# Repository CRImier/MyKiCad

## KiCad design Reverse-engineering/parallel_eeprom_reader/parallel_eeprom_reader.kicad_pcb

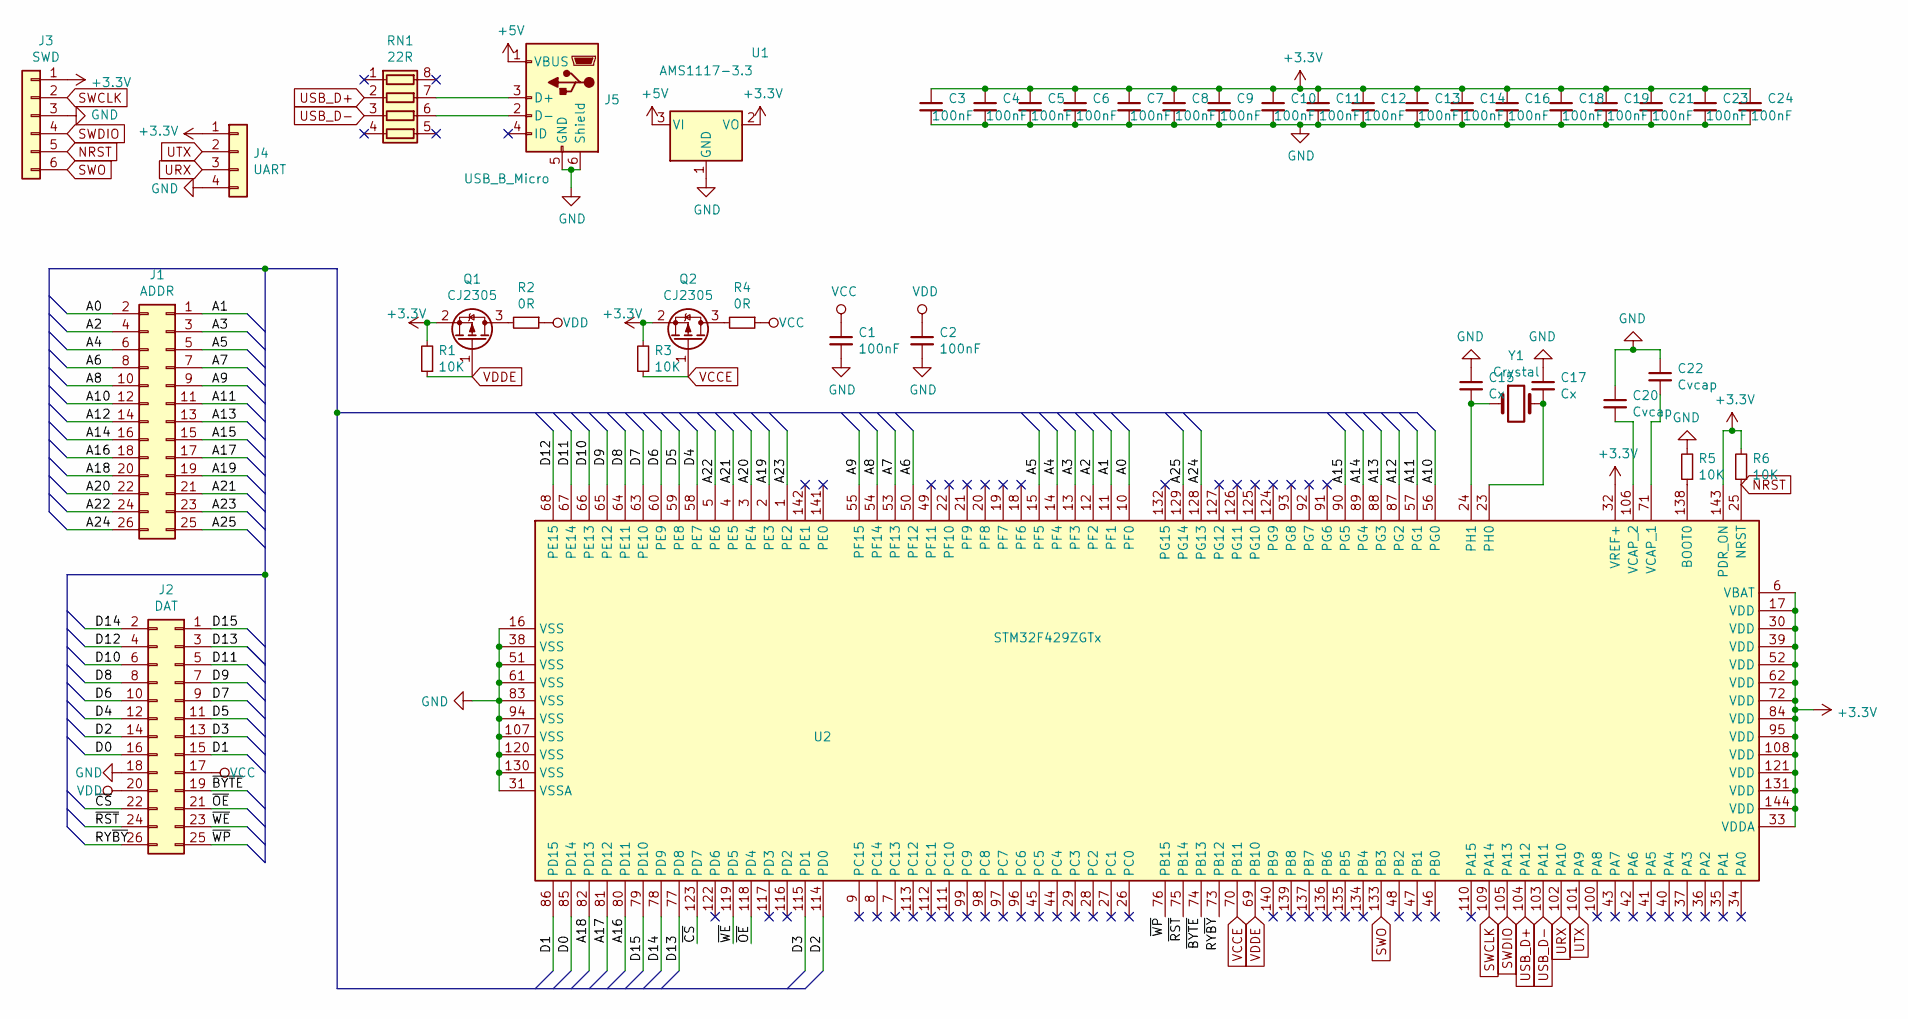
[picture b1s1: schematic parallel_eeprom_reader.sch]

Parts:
C1, C2, C3, C4, C5, C6, C7, C8, C9, C10, C11, C12, C13, C14, C16, C18, C19, C21, C23, C24: 100nF; C_0402_1005Metric
C15, C17: Cx; C_0603_1608Metric
C20, C22: Cvcap; C_0603_1608Metric
J1: ADDR; PinSocket_2x13_P2.00mm_Vertical_SMD
J2: DAT; PinSocket_2x13_P2.00mm_Vertical_SMD
J3: SWD; PinSocket_1x06_P2.54mm_Vertical
J4: UART; PinSocket_2x02_P2.00mm_Vertical
J5: USB_B_Micro; MICROUSB_SIMPLE
Q1, Q2: CJ2305; SOT-23
R1, R3, R5, R6: 10K; R_0402_1005Metric
R2, R4: 0R; R_0402_1005Metric
RN1: 22R; R_Array_Concave_4x0603
U1: AMS1117-3.3; SOT-223-3_TabPin2
U2: STM32F429ZGTx; LQFP-144_20x20mm_P0.5mm
Y1: Crystal; Crystal_SMD_5032-2Pin_5.0x3.2mm_HandSoldering

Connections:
+3V3: C3.1, C4.1, C5.1, C6.1, C7.1, C8.1, C9.1, C10.1, C11.1, C12.1, C13.1, C14.1, C16.1, C18.1, C19.1, C21.1, C23.1, C24.1, J3.1, J4.1, Q1.2 (S), Q2.2 (S), R1.2, R3.2, R6.2, U1.2 (VO), U2.6 (VBAT), U2.17 (VDD), U2.30 (VDD), U2.32 (VREF+), U2.33 (VDDA), U2.39 (VDD), U2.52 (VDD), U2.62 (VDD), U2.72 (VDD), U2.84 (VDD), U2.95 (VDD), U2.108 (VDD), U2.121 (VDD), U2.131 (VDD), U2.143 (PDR_ON), U2.144 (VDD)
+5V: J5.1 (VBUS), U1.3 (VI)
/A0: J1.2, U2.10 (PF0)
/A1: J1.1, U2.11 (PF1)
/A2: J1.4, U2.12 (PF2)
/A3: J1.3, U2.13 (PF3)
/A4: J1.6, U2.14 (PF4)
/A5: J1.5, U2.15 (PF5)
/A6: J1.8, U2.50 (PF12)
/A7: J1.7, U2.53 (PF13)
/A8: J1.10, U2.54 (PF14)
/A9: J1.9, U2.55 (PF15)
/A10: J1.12, U2.56 (PG0)
/A11: J1.11, U2.57 (PG1)
/A12: J1.14, U2.87 (PG2)
/A13: J1.13, U2.88 (PG3)
/A14: J1.16, U2.89 (PG4)
/A15: J1.15, U2.90 (PG5)
/A16: J1.18, U2.80 (PD11)
/A17: J1.17, U2.81 (PD12)
/A18: J1.20, U2.82 (PD13)
/A19: J1.19, U2.2 (PE3)
/A20: J1.22, U2.3 (PE4)
/A21: J1.21, U2.4 (PE5)
/A22: J1.24, U2.5 (PE6)
/A23: J1.23, U2.1 (PE2)
/A24: J1.26, U2.128 (PG13)
/A25: J1.25, U2.129 (PG14)
/D0: J2.16, U2.85 (PD14)
/D1: J2.15, U2.86 (PD15)
/D2: J2.14, U2.114 (PD0)
/D3: J2.13, U2.115 (PD1)
/D4: J2.12, U2.58 (PE7)
/D5: J2.11, U2.59 (PE8)
/D6: J2.10, U2.60 (PE9)
/D7: J2.9, U2.63 (PE10)
/D8: J2.8, U2.64 (PE11)
/D9: J2.7, U2.65 (PE12)
/D10: J2.6, U2.66 (PE13)
/D11: J2.5, U2.67 (PE14)
/D12: J2.4, U2.68 (PE15)
/D13: J2.3, U2.77 (PD8)
/D14: J2.2, U2.78 (PD9)
/D15: J2.1, U2.79 (PD10)
/RY~BY: J2.26, U2.73 (PB12)
/~BYTE: J2.19, U2.74 (PB13)
/~CS: J2.22, U2.123 (PD7)
/~OE: J2.21, U2.118 (PD4)
/~RST: J2.24, U2.75 (PB14)
/~WE: J2.23, U2.119 (PD5)
/~WP: J2.25, U2.76 (PB15)
GND: C1.2, C2.2, C3.2, C4.2, C5.2, C6.2, C7.2, C8.2, C9.2, C10.2, C11.2, C12.2, C13.2, C14.2, C15.1, C16.2, C17.1, C18.2, C19.2, C20.1, C21.2, C22.1, C23.2, C24.2, J2.18, J3.3, J4.4, J5.5 (GND), J5.6 (Shield), R5.2, U1.1 (GND), U2.16 (VSS), U2.31 (VSSA), U2.38 (VSS), U2.51 (VSS), U2.61 (VSS), U2.83 (VSS), U2.94 (VSS), U2.107 (VSS), U2.120 (VSS), U2.130 (VSS)
NRST: J3.5, R6.1, U2.25 (NRST)
unnamed: C15.2, U2.24 (PH1), Y1.1
unnamed: C17.2, U2.23 (PH0), Y1.2
unnamed: C20.2, U2.106 (VCAP_2)
unnamed: C22.2, U2.71 (VCAP_1)
unnamed: J5.2 (D-), RN1.6 (R3.2)
unnamed: J5.3 (D+), RN1.7 (R2.2)
unnamed: Q1.3 (D), R2.2
unnamed: Q2.3 (D), R4.2
unnamed: R5.1, U2.138 (BOOT0)
SWCLK: J3.2, U2.109 (PA14)
SWDIO: J3.4, U2.105 (PA13)
SWO: J3.6, U2.133 (PB3)
URX: J4.3, U2.102 (PA10)
USB_D+: RN1.2 (R2.1), U2.104 (PA12)
USB_D-: RN1.3 (R3.1), U2.103 (PA11)
UTX: J4.2, U2.101 (PA9)
VCC: C1.1, J2.17, R4.1
VCCE: Q2.1 (G), R3.1, U2.70 (PB11)
VDD: C2.1, J2.20, R2.1
VDDE: Q1.1 (G), R1.1, U2.69 (PB10)

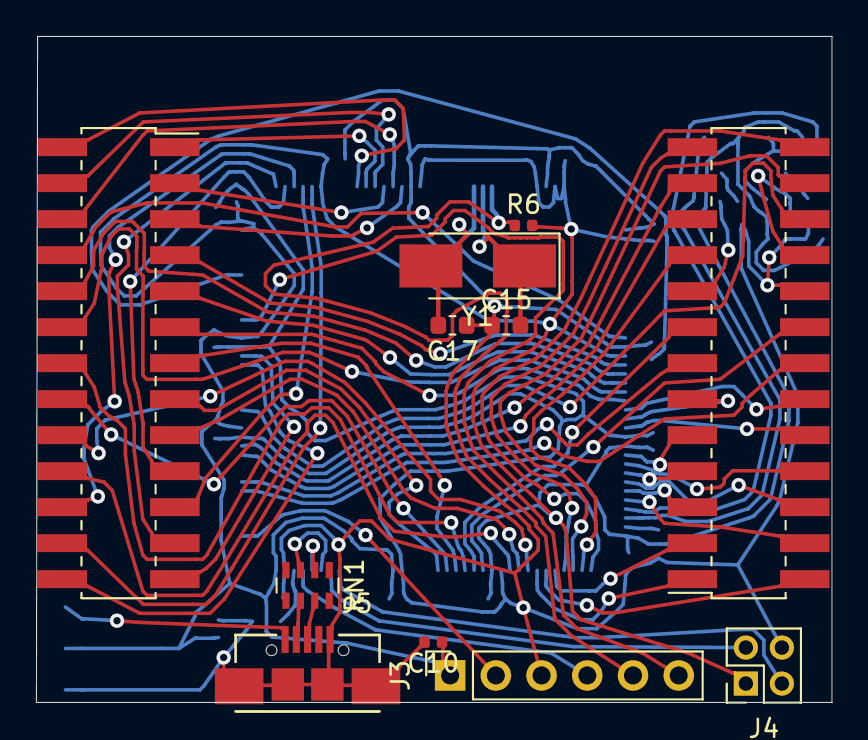
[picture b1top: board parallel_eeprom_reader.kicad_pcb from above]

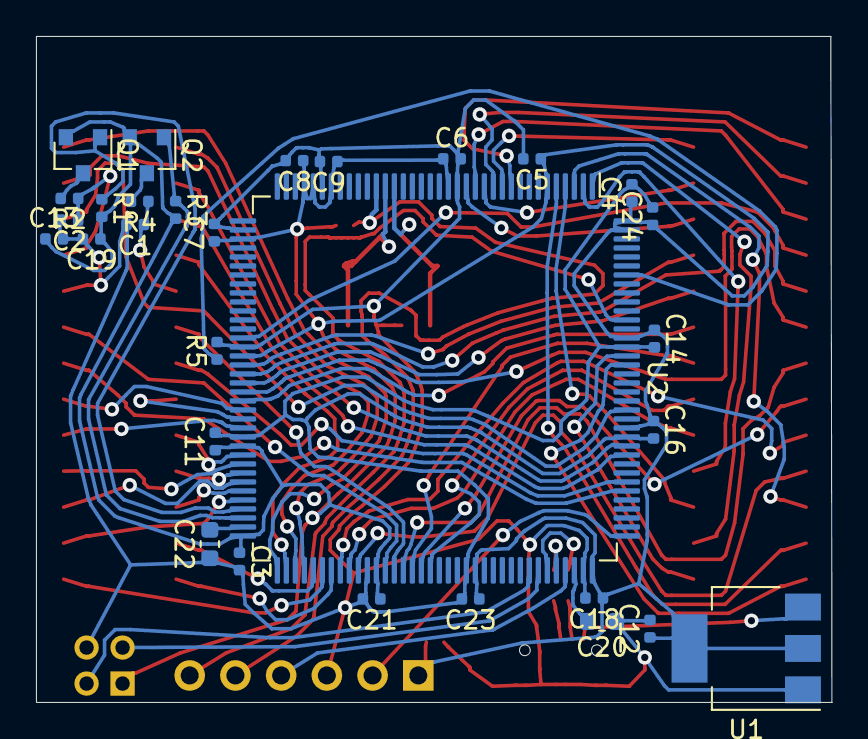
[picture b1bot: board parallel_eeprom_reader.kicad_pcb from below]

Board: 2 copper layers, 44.2 x 37.0 mm, 41 parts (30 on the bottom side), 73 nets.

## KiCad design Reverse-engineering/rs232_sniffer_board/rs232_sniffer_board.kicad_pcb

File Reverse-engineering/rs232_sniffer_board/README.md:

# RS232 sniffer board

An unfinished board for RS232-on-DB9 sniffing, up to 5 RX channels and 3 TX.
Consider it a template. TODO's in the schematic.

Name's Margaret. Likes peaches and popsicles ^~^

## Notes

- This board is untested and there's no guarantees of fitness.

## Info

- Software: Kicad 7
- Version: 0
- PCB size: 76x45mm
- Layer count: 2

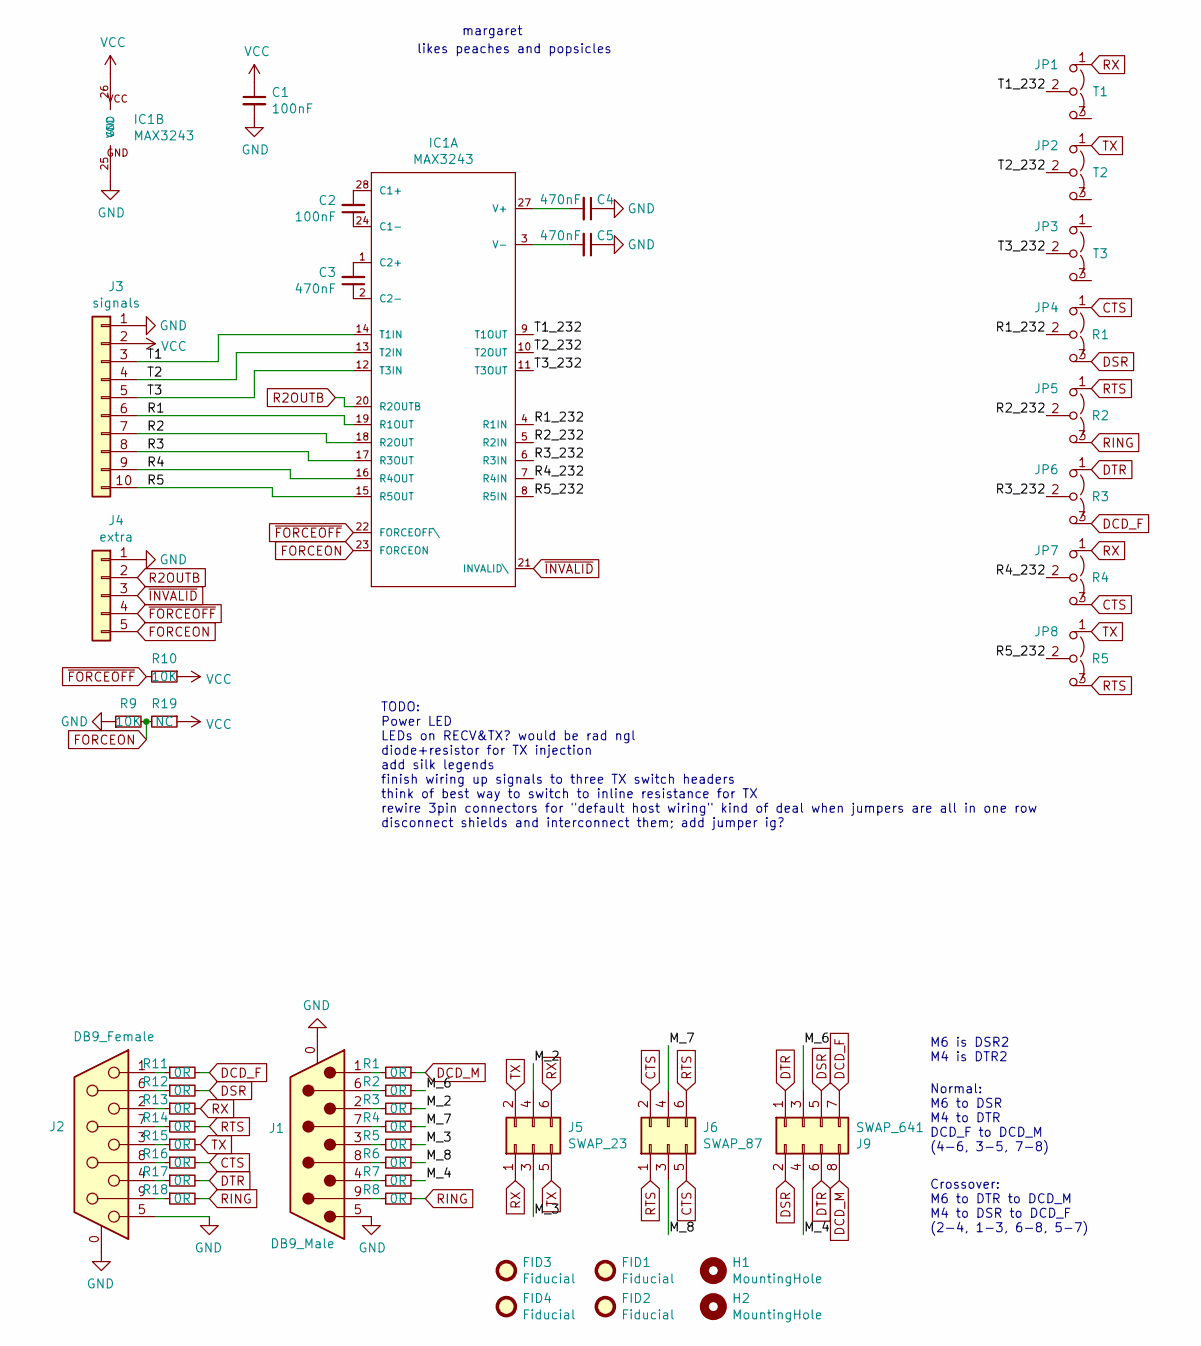
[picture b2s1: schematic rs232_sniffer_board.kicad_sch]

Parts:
C1, C2: 100nF; C_0805_2012Metric
C3, C4, C5: 470nF; C_0805_2012Metric
FID1, FID2, FID3, FID4: Fiducial; Fiducial_1.5mm_Mask3mm
H1, H2: MountingHole; MountingHole_5mm
IC1: MAX3243; SSOP-28_5.3x10.2mm_P0.65mm
J1: DB9_Male; DSUB-9_Male_Horizontal_P2.77x2.84mm_EdgePinOffset4.94mm_Hou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
J2: DB9_Female; DSUB-9_Female_Horizontal_P2.77x2.84mm_EdgePinOffset4.94mm_H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
J3: signals; PinHeader_1x10_P2.54mm_Vertical
J4: extra; PinHeader_1x05_P2.54mm_Vertical
J5: SWAP_23; PinHeader_2x03_P2.54mm_Vertical
J6: SWAP_87; PinHeader_2x03_P2.54mm_Vertical
J9: SWAP_641; PinHeader_2x04_P2.54mm_Vertical
JP1: T1; PinHeader_1x03_P2.54mm_Vertical
JP2: T2; PinHeader_1x03_P2.54mm_Vertical
JP3: T3; PinHeader_1x03_P2.54mm_Vertical
JP4: R1; PinHeader_1x03_P2.54mm_Vertical
JP5: R2; PinHeader_1x03_P2.54mm_Vertical
JP6: R3; PinHeader_1x03_P2.54mm_Vertical
JP7: R4; PinHeader_1x03_P2.54mm_Vertical
JP8: R5; PinHeader_1x03_P2.54mm_Vertical
R1, R2, R3, R4, R5, R6, R7, R8, R11, R12, R13, R14, R15, R16, R17, R18: 0R; R_0805_2012Metric
R9, R10: 10K; R_0805_2012Metric
R19: NC; R_0805_2012Metric

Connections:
/M_2: J5.4, R3.1
/M_3: J5.3, R5.1
/M_4: J9.4, R7.1
/M_6: J9.3, R2.1
/M_7: J6.4, R4.1
/M_8: J6.3, R6.1
/R1: IC1.19 (R1OUT), J3.6
/R1_232: IC1.4 (R1IN), JP4.2 (C)
/R2: IC1.18 (R2OUT), J3.7
/R2_232: IC1.5 (R2IN), JP5.2 (C)
/R3: IC1.17 (R3OUT), J3.8
/R3_232: IC1.6 (R3IN), JP6.2 (C)
/R4: IC1.16 (R4OUT), J3.9
/R4_232: IC1.7 (R4IN), JP7.2 (C)
/R5: IC1.15 (R5OUT), J3.10
/R5_232: IC1.8 (R5IN), JP8.2 (C)
/T1: IC1.14 (T1IN), J3.3
/T1_232: IC1.9 (T1OUT), JP1.2 (C)
/T2: IC1.13 (T2IN), J3.4
/T2_232: IC1.10 (T2OUT), JP2.2 (C)
/T3: IC1.12 (T3IN), J3.5
/T3_232: IC1.11 (T3OUT), JP3.2 (C)
CTS: J6.2, J6.5, JP4.1 (A), JP7.3 (B), R16.2
DCD_F: J9.7, JP6.3 (B), R11.2
DCD_M: J9.8, R1.1
DSR: J9.2, J9.5, JP4.3 (B), R12.2
DTR: J9.1, J9.6, JP6.1 (A), R17.2
FORCEON: IC1.23 (FORCEON), J4.5, R9.2, R19.2
GND: C1.2, C4.1, C5.1, IC1.25 (GND), J1.0 (PAD), J1.5, J2.0 (PAD), J2.5, J3.1, J4.1, R9.1
unnamed: C2.2, IC1.28 (C1+)
unnamed: C2.1, IC1.24 (C1-)
unnamed: C3.2, IC1.1 (C2+)
unnamed: C3.1, IC1.2 (C2-)
unnamed: C4.2, IC1.27 (V+)
unnamed: C5.2, IC1.3 (V-)
unnamed: J1.1, R1.2
unnamed: J1.2, R3.2
unnamed: J1.3, R5.2
unnamed: J1.4, R7.2
unnamed: J1.6, R2.2
unnamed: J1.7, R4.2
unnamed: J1.8, R6.2
unnamed: J1.9, R8.2
unnamed: J2.1, R11.1
unnamed: J2.2, R13.1
unnamed: J2.3, R15.1
unnamed: J2.4, R17.1
unnamed: J2.6, R12.1
unnamed: J2.7, R14.1
unnamed: J2.8, R16.1
unnamed: J2.9, R18.1
R2OUTB: IC1.20 (R2OUTB), J4.2
RING: JP5.3 (B), R8.1, R18.2
RTS: J6.1, J6.6, JP5.1 (A), JP8.3 (B), R14.2
RX: J5.1, J5.6, JP1.1 (A), JP7.1 (A), R13.2
TX: J5.2, J5.5, JP2.1 (A), JP8.1 (A), R15.2
VCC: C1.1, IC1.26 (VCC), J3.2, R10.1, R19.1
~FORCEOFF: IC1.22 (FORCEOFF\), J4.4, R10.2
~INVALID: IC1.21 (INVALID\), J4.3

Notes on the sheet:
margaret
Crossover: M6 to DTR to DCD_M M4 to DSR to DCD_F (2-4, 1-3, 6-8, 5-7)
M6 is DSR2 M4 is DTR2
TODO: Power LED LEDs on RECV&TX? would be rad ngl diode+resistor for TX injection add silk legends finish wiring up signals to three TX switch headers think of best way to switch to inline resistance for TX rewire 3pin connectors for "default host wiring" kind of deal when jumpers are all in one ro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
likes peaches and popsicles
Normal: M6 to DSR M4 to DTR DCD_F to DCD_M (4-6, 3-5, 7-8)

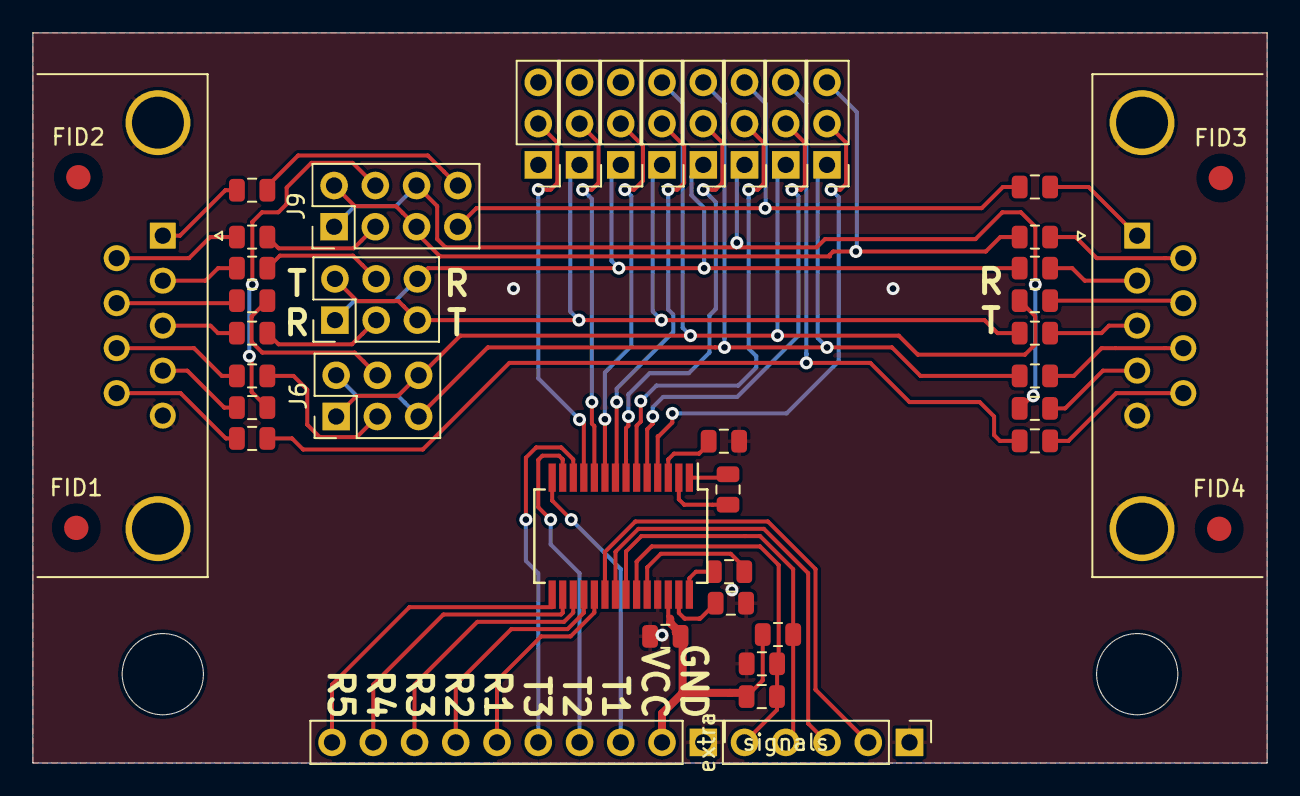
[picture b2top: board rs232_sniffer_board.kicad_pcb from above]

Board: 2 copper layers, 76.0 x 45.0 mm, 46 parts (0 on the bottom side), 59 nets.

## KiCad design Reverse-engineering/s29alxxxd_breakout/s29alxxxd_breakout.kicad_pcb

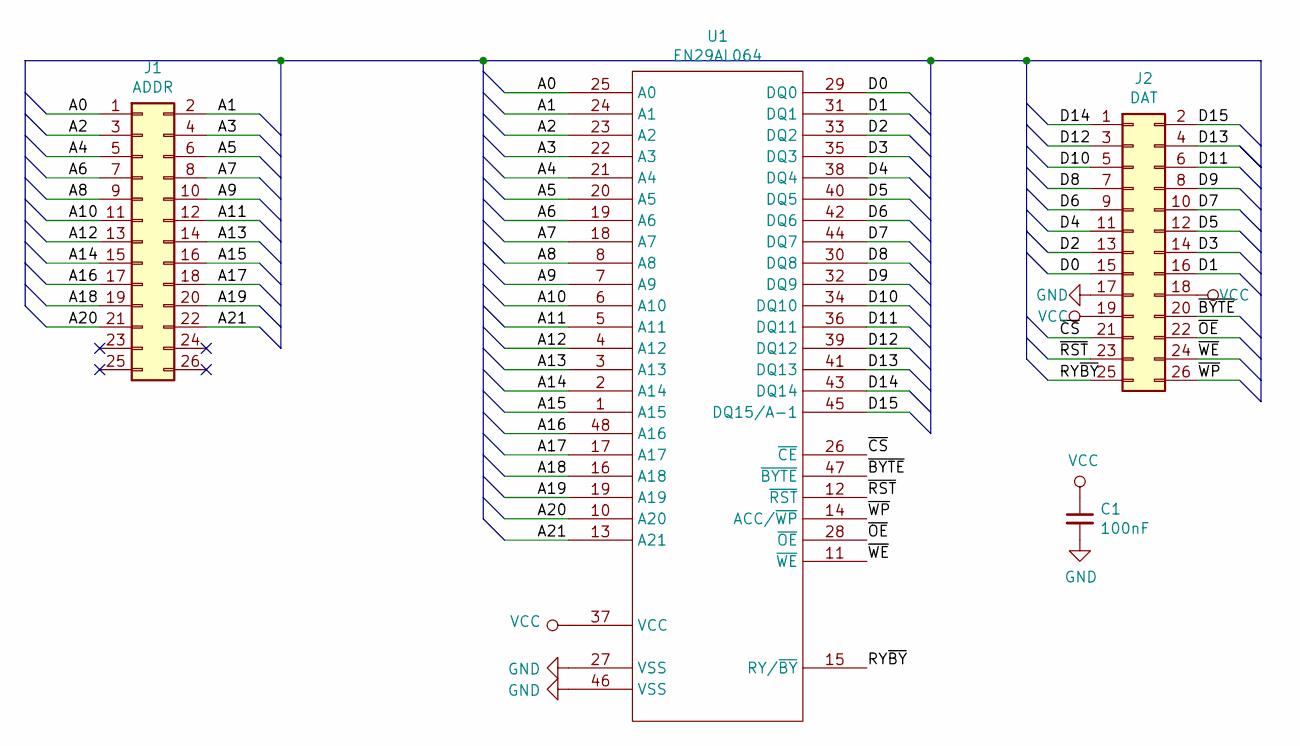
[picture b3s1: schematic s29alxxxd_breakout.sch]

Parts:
C1: 100nF; C_0805_2012Metric
J1: ADDR; PinSocket_2x13_P2.00mm_Vertical_SMD
J2: DAT; PinSocket_2x13_P2.00mm_Vertical_SMD
U1: EN29AL064; TSOP-I-48_18.4x12mm_P0.5mm

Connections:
/A0: J1.1, U1.25 (A0)
/A1: J1.2, U1.24 (A1)
/A2: J1.3, U1.23 (A2)
/A3: J1.4, U1.22 (A3)
/A4: J1.5, U1.21 (A4)
/A5: J1.6, U1.20 (A5)
/A7: J1.8, U1.18 (A7)
/A8: J1.9, U1.8 (A8)
/A9: J1.10, U1.7 (A9)
/A10: J1.11, U1.6 (A10)
/A11: J1.12, U1.5 (A11)
/A12: J1.13, U1.4 (A12)
/A13: J1.14, U1.3 (A13)
/A14: J1.15, U1.2 (A14)
/A15: J1.16, U1.1 (A15)
/A16: J1.17, U1.48 (A16)
/A17: J1.18, U1.17 (A17)
/A18: J1.19, U1.16 (A18)
/A20: J1.21, U1.10 (A20)
/A21: J1.22, U1.13 (A21)
/D0: J2.15, U1.29 (DQ0)
/D1: J2.16, U1.31 (DQ1)
/D2: J2.13, U1.33 (DQ2)
/D3: J2.14, U1.35 (DQ3)
/D4: J2.11, U1.38 (DQ4)
/D5: J2.12, U1.40 (DQ5)
/D6: J2.9, U1.42 (DQ6)
/D7: J2.10, U1.44 (DQ7)
/D8: J2.7, U1.30 (DQ8)
/D9: J2.8, U1.32 (DQ9)
/D10: J2.5, U1.34 (DQ10)
/D11: J2.6, U1.36 (DQ11)
/D12: J2.3, U1.39 (DQ12)
/D13: J2.4, U1.41 (DQ13)
/D14: J2.1, U1.43 (DQ14)
/D15: J2.2, U1.45 (DQ15/A-1)
/RY~BY: J2.25, U1.15 (RY/~BY)
/~BYTE: J2.20, U1.47 (~BYTE)
/~CS: J2.21, U1.26 (~CE)
/~OE: J2.22, U1.28 (~OE)
/~RST: J2.23, U1.12 (~RST)
/~WE: J2.24, U1.11 (~WE)
/~WP: J2.26, U1.14 (ACC/~WP)
GND: C1.2, J2.17, U1.27 (VSS), U1.46 (VSS)
VCC: C1.1, J2.18, J2.19, U1.37 (VCC)

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
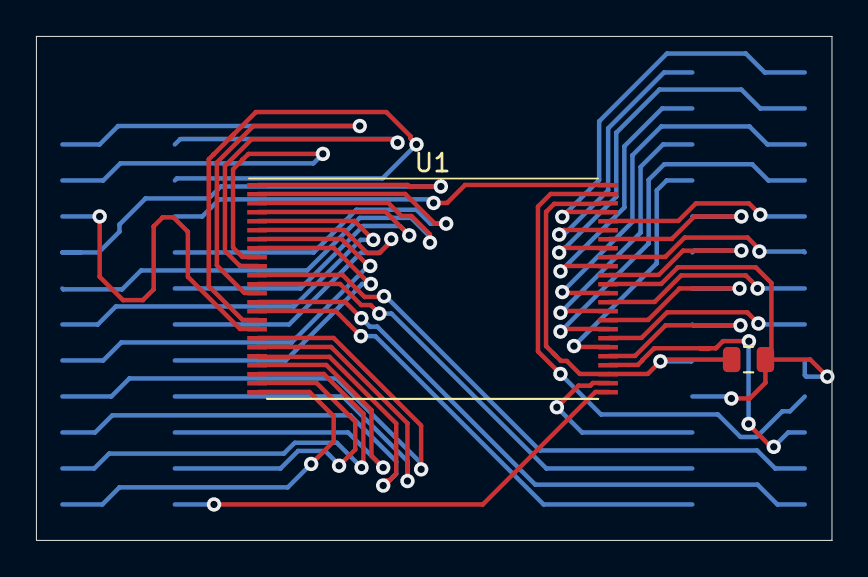
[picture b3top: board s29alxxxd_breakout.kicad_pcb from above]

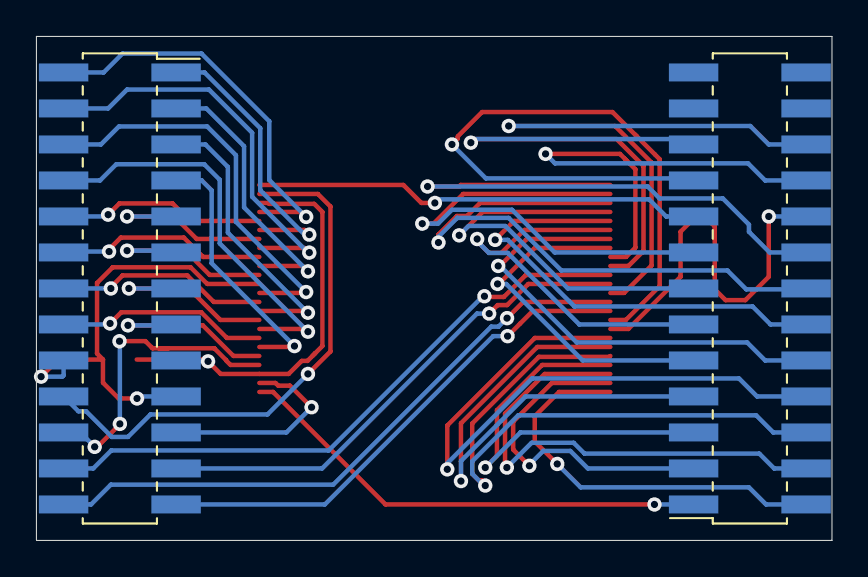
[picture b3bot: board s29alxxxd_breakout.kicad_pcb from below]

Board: 2 copper layers, 44.2 x 28.0 mm, 4 parts (2 on the bottom side), 47 nets.

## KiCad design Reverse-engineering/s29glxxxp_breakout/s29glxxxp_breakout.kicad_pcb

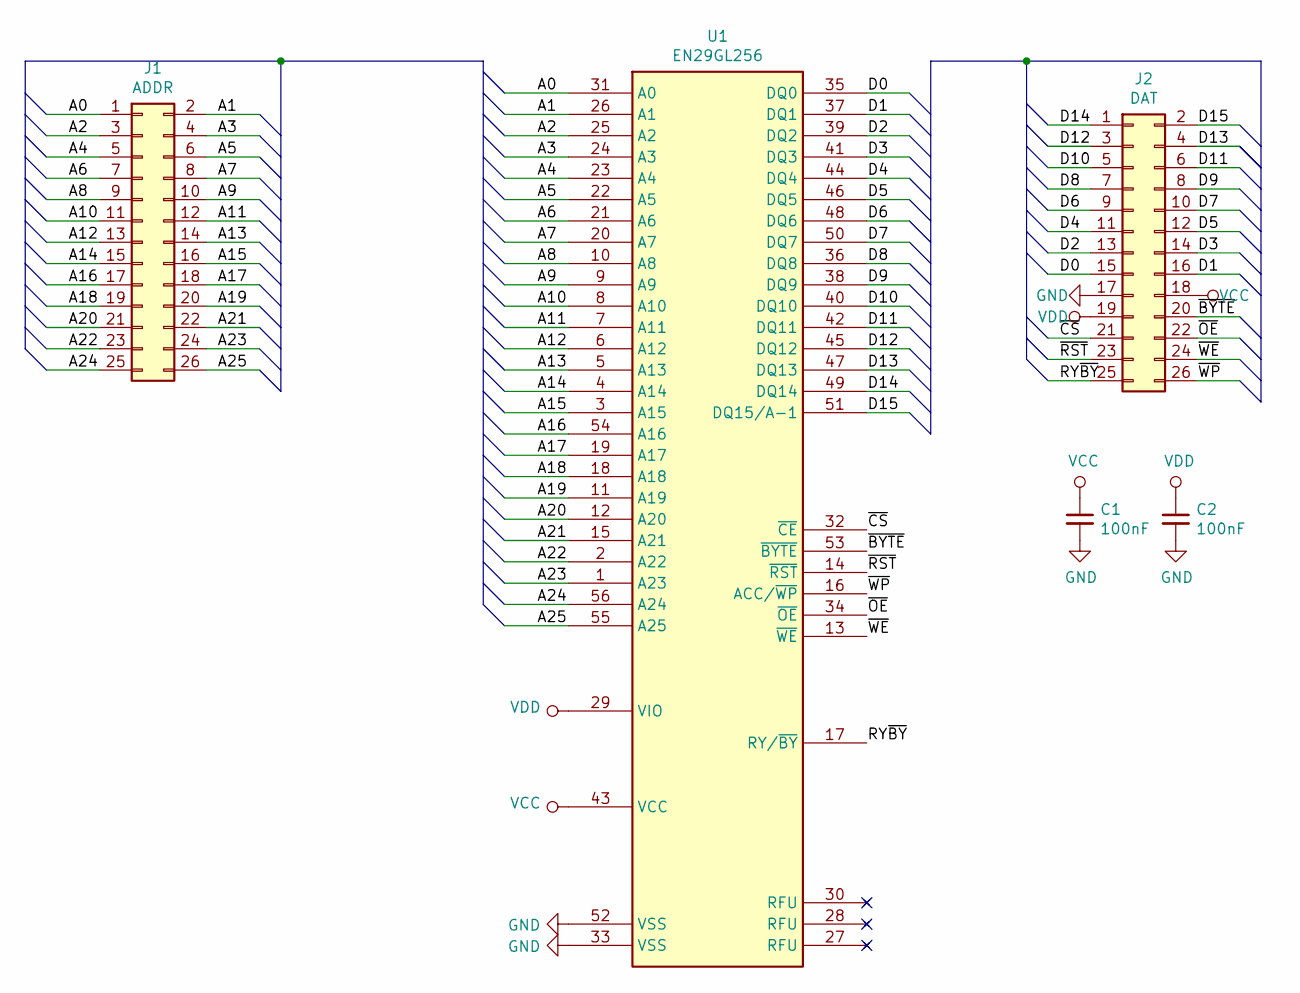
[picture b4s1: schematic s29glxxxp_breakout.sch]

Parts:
C1, C2: 100nF; C_0805_2012Metric
J1: ADDR; PinSocket_2x13_P2.00mm_Vertical_SMD
J2: DAT; PinSocket_2x13_P2.00mm_Vertical_SMD
U1: EN29GL256; TSOP-I-56_18.4x14mm_P0.5mm

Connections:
/A0: J1.1, U1.31 (A0)
/A1: J1.2, U1.26 (A1)
/A2: J1.3, U1.25 (A2)
/A3: J1.4, U1.24 (A3)
/A4: J1.5, U1.23 (A4)
/A5: J1.6, U1.22 (A5)
/A6: J1.7, U1.21 (A6)
/A7: J1.8, U1.20 (A7)
/A8: J1.9, U1.10 (A8)
/A9: J1.10, U1.9 (A9)
/A10: J1.11, U1.8 (A10)
/A11: J1.12, U1.7 (A11)
/A12: J1.13, U1.6 (A12)
/A13: J1.14, U1.5 (A13)
/A14: J1.15, U1.4 (A14)
/A15: J1.16, U1.3 (A15)
/A16: J1.17, U1.54 (A16)
/A17: J1.18, U1.19 (A17)
/A18: J1.19, U1.18 (A18)
/A19: J1.20, U1.11 (A19)
/A20: J1.21, U1.12 (A20)
/A21: J1.22, U1.15 (A21)
/A22: J1.23, U1.2 (A22)
/A23: J1.24, U1.1 (A23)
/A24: J1.25, U1.56 (A24)
/A25: J1.26, U1.55 (A25)
/D0: J2.15, U1.35 (DQ0)
/D1: J2.16, U1.37 (DQ1)
/D2: J2.13, U1.39 (DQ2)
/D3: J2.14, U1.41 (DQ3)
/D4: J2.11, U1.44 (DQ4)
/D5: J2.12, U1.46 (DQ5)
/D6: J2.9, U1.48 (DQ6)
/D7: J2.10, U1.50 (DQ7)
/D8: J2.7, U1.36 (DQ8)
/D9: J2.8, U1.38 (DQ9)
/D10: J2.5, U1.40 (DQ10)
/D11: J2.6, U1.42 (DQ11)
/D12: J2.3, U1.45 (DQ12)
/D13: J2.4, U1.47 (DQ13)
/D14: J2.1, U1.49 (DQ14)
/D15: J2.2, U1.51 (DQ15/A-1)
/RY~BY: J2.25, U1.17 (RY/~BY)
/~BYTE: J2.20, U1.53 (~BYTE)
/~CS: J2.21, U1.32 (~CE)
/~OE: J2.22, U1.34 (~OE)
/~RST: J2.23, U1.14 (~RST)
/~WE: J2.24, U1.13 (~WE)
/~WP: J2.26, U1.16 (ACC/~WP)
GND: C1.2, C2.2, J2.17, U1.33 (VSS), U1.52 (VSS)
VCC: C1.1, J2.18, U1.43 (VCC)
VDD: C2.1, J2.19, U1.29 (VIO)

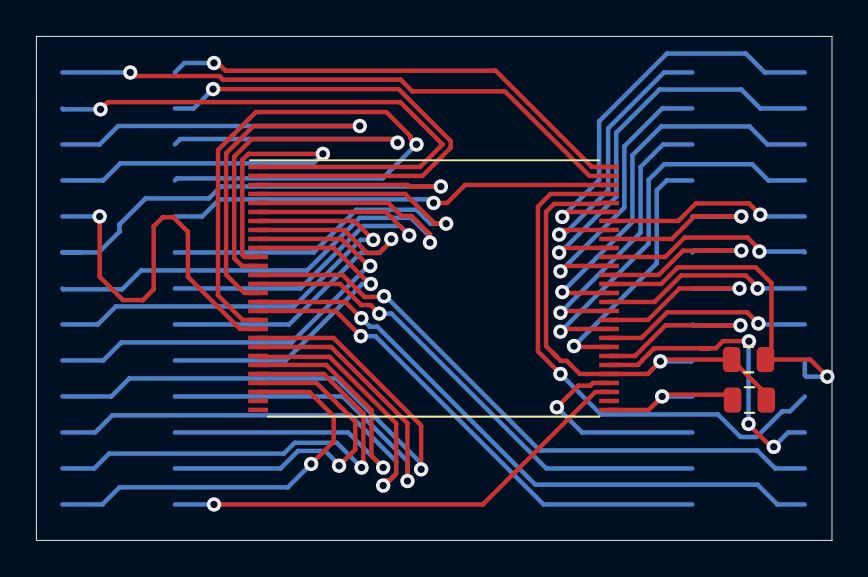
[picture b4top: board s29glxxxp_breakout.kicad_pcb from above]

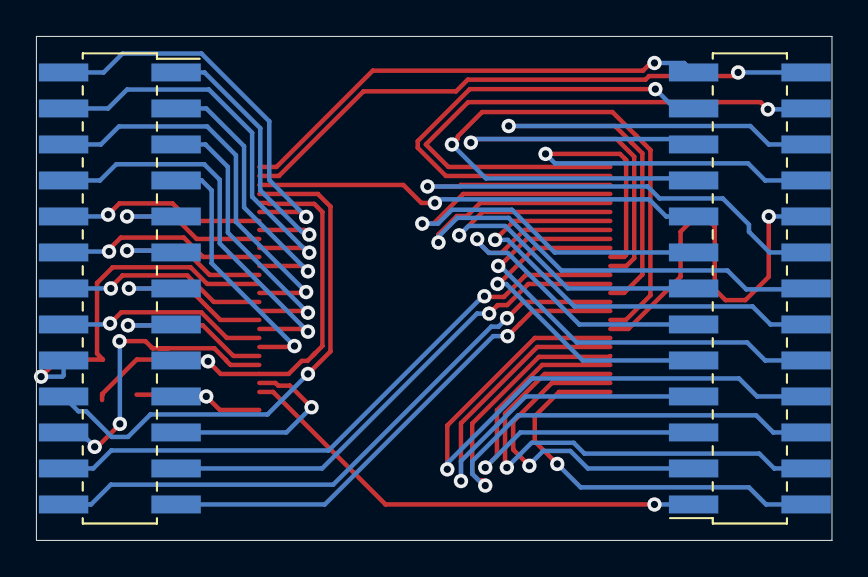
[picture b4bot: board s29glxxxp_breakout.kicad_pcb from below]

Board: 2 copper layers, 44.2 x 28.0 mm, 5 parts (2 on the bottom side), 52 nets.

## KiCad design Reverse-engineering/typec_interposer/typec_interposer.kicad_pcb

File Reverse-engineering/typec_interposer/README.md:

#  Type-C interposer

This is a passthrough Type-C adapter that exposes VBUS, D+/- and CC1/2 signals on pin headers. I designed it so that you can 
sniff and intercept Type-C communications. This adapter also allows you to interrupt D+/-, CC1/2 or SBU1/2 signals by 
removing 0603 resistors, in case that's useful on your Type-C journey - maybe you need to spoof a signal or two, or make a 
USB-C condom out of an adapter you have on hand.

Type-C communication is part analog, part digital. Analog communications, you should be able to sniff with a resistor or an 
oscilloscope. If voltages higher than 5V or USB-C alt modes are requested, there's going to be a digital component to that, 
and you can sniff it with a logic analyzer. You can also sniff any chargers with proprietary or cryptography-involving 
communication protocols - i.e. HP laptop chargers that

This adapter doesn't support 3.0 or DisplayPort or HDMI, as it doesn't pass any of the high-speed pairs through. When I'll be 
working on my next batch of PCBs, I'll make some 3.0 adapters if I sell enough of these ones!

You need a logic analyzer, still. However, you can get one for $5, and if you don't have, you ought to get one right away. 
With a combination of sigrok + Pulseview, both being open-source and free, you can instantly join the world of debugging 
Type-C connections. 

USB C-C cables only have one CC wire in them, so if you don't get a CC connection with this adapter, you might need to, 
ironically, flip one of the cables you're using for the connection.

Signal names aren't silkscreened on this board, but the next version will have them silkscreened.

This board is untested and there's no guarantees of fitness.

- PCB size: 28x10.6mm
- Layer count: 2

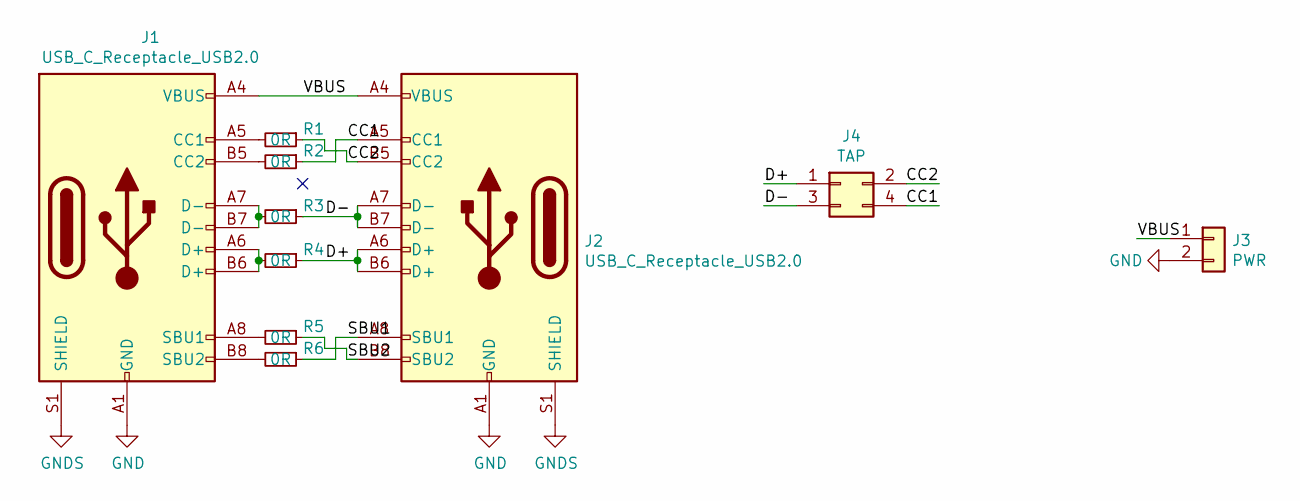
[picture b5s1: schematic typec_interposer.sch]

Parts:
J1, J2: USB_C_Receptacle_USB2.0; USB_C_Receptacle_HRO_TYPE-C-31-M-12
J3: PWR; PinHeader_1x02_P2.54mm_Vertical
J4: TAP; PinHeader_2x02_P2.54mm_Vertical
R1, R2, R3, R4, R5, R6: 0R; R_0603_1608Metric

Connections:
/CC1: J2.A5 (CC1), J4.4, R2.1
/CC2: J2.B5 (CC2), J4.2, R1.1
/D+: J2.A6 (D+), J2.B6 (D+), J4.1, R4.1
/D-: J2.A7 (D-), J2.B7 (D-), J4.3, R3.1
/SBU1: J2.A8 (SBU1), R6.1
/SBU2: J2.B8 (SBU2), R5.1
/VBUS: J1.A4 (VBUS), J1.A9 (VBUS), J1.B4 (VBUS), J1.B9 (VBUS), J2.A4 (VBUS), J2.A9 (VBUS), J2.B4 (VBUS), J2.B9 (VBUS), J3.1
GND: J1.A1 (GND), J1.A12 (GND), J1.B1 (GND), J1.B12 (GND), J2.A1 (GND), J2.A12 (GND), J2.B1 (GND), J2.B12 (GND), J3.2
GNDS: J1.S1 (SHIELD), J2.S1 (SHIELD)
unnamed: J1.A5 (CC1), R1.2
unnamed: J1.A6 (D+), J1.B6 (D+), R4.2
unnamed: J1.A7 (D-), J1.B7 (D-), R3.2
unnamed: J1.A8 (SBU1), R5.2
unnamed: J1.B5 (CC2), R2.2
unnamed: J1.B8 (SBU2), R6.2

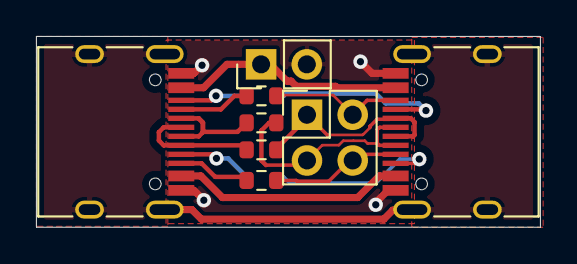
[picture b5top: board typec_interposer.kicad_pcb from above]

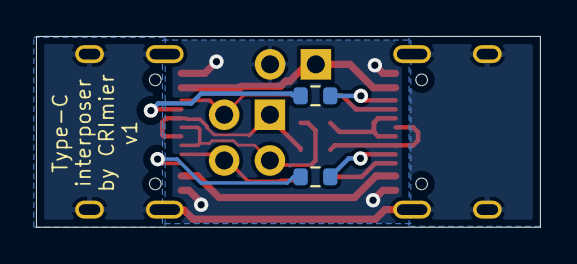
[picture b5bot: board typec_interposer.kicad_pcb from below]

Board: 2 copper layers, 28.0 x 10.6 mm, 10 parts (2 on the bottom side), 15 nets.

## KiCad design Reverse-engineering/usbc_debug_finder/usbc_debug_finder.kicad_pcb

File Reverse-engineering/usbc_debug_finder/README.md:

# USB-C signal finder

This tester plugs into a USB-C port for probing every single signal of it
for IC-connected signals. It uses the IC-internal ESD diodes for detection,
and a separate coin cell to create negative voltage relative to GND.

You can use this for checking if the USB-C port supports high-speed operation,
or if any signals are exposed on SBU.

Some back-of-napkin guidelines:

- If HS signals are present but SBU aren't, then the port is capable of USB3
- If SBU and HS signals are present, then the port is capable of DP or Thunderbolt; alternatively, it does USB3 and support debug/passive audio on SBU.
- If SBU is present but HS isn't, there is either debug or passive audio adapter support
- If CC signals aren't present, then the port isn't capable of CC monitoring/communications, which also excludes all of the above

Get in touch with me if you find out any of these to be incorrect.

It's normal for both D+ and D- pairs to be present; they're there for 'just in case' purposes.
If only one of these is present on some port of yours, let me know ;-P

This tester doesn't probe VBUS, and of course, GND.

I'm not responsible if this damages a USB-C port of yours, or not-yours.

The footprint for the USB-C plug is intended to work both for the Molex 105444 plug,
as well as the XKB Connectivity U261-241N-4BS60 plug.

## Notes

- Signal names are silkscreened on the board's top layer.
- This board is untested and there's no guarantees of fitness.

## Info

- Software: Kicad 6
- Version: 1
- PCB size: 28x11mm
- Layer count: 2
- Recommended thickness: 0.8mm or 1mm (for USB-C plug)

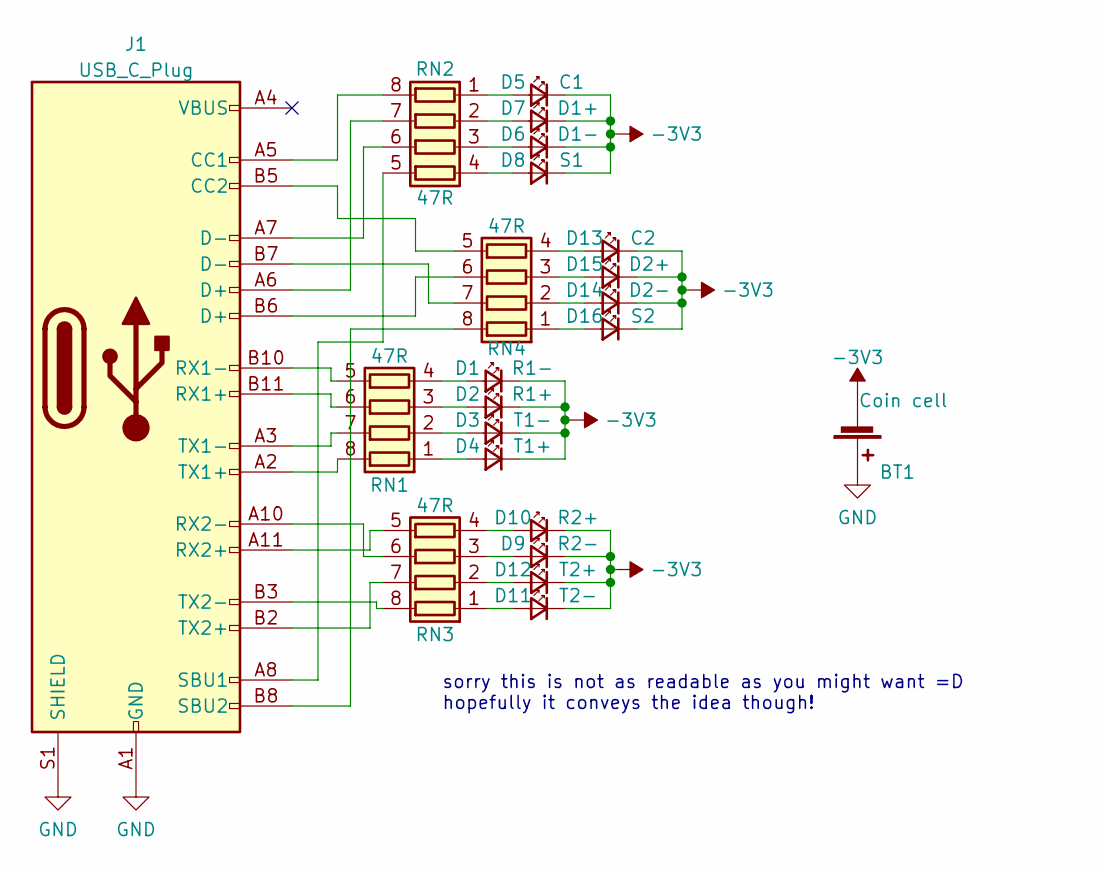
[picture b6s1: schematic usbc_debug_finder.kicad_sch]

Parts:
BT1: Coin cell; BAT-TH_BS-05-A1BJ001
D1: R1-; LED_0603_1608Metric
D2: R1+; LED_0603_1608Metric
D3: T1-; LED_0603_1608Metric
D4: T1+; LED_0603_1608Metric
D5: C1; LED_0603_1608Metric
D6: D1-; LED_0603_1608Metric
D7: D1+; LED_0603_1608Metric
D8: S1; LED_0603_1608Metric
D9: R2-; LED_0603_1608Metric
D10: R2+; LED_0603_1608Metric
D11: T2-; LED_0603_1608Metric
D12: T2+; LED_0603_1608Metric
D13: C2; LED_0603_1608Metric
D14: D2-; LED_0603_1608Metric
D15: D2+; LED_0603_1608Metric
D16: S2; LED_0603_1608Metric
J1: USB_C_Plug; USB_C_Plug_Molex_105444
RN1, RN2, RN3, RN4: 47R; R_Array_Concave_4x0603

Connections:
-3V3: BT1.2 (-), D1.1 (K), D2.1 (K), D3.1 (K), D4.1 (K), D5.1 (K), D6.1 (K), D7.1 (K), D8.1 (K), D9.1 (K), D10.1 (K), D11.1 (K), D12.1 (K), D13.1 (K), D14.1 (K), D15.1 (K), D16.1 (K)
GND: BT1.1 (+), J1.A1 (GND), J1.A12 (GND), J1.B1 (GND), J1.B12 (GND), J1.S1 (SHIELD)
unnamed: D1.2 (A), RN1.4 (R4.1)
unnamed: D2.2 (A), RN1.3 (R3.1)
unnamed: D3.2 (A), RN1.2 (R2.1)
unnamed: D4.2 (A), RN1.1 (R1.1)
unnamed: D5.2 (A), RN2.1 (R1.1)
unnamed: D6.2 (A), RN2.3 (R3.1)
unnamed: D7.2 (A), RN2.2 (R2.1)
unnamed: D8.2 (A), RN2.4 (R4.1)
unnamed: D9.2 (A), RN3.3 (R3.1)
unnamed: D10.2 (A), RN3.4 (R4.1)
unnamed: D11.2 (A), RN3.1 (R1.1)
unnamed: D12.2 (A), RN3.2 (R2.1)
unnamed: D13.2 (A), RN4.4 (R4.1)
unnamed: D14.2 (A), RN4.2 (R2.1)
unnamed: D15.2 (A), RN4.3 (R3.1)
unnamed: D16.2 (A), RN4.1 (R1.1)
unnamed: J1.A5 (CC1), RN2.8 (R1.2)
unnamed: J1.B5 (CC2), RN4.5 (R4.2)
unnamed: J1.B11 (RX1+), RN1.6 (R3.2)
unnamed: J1.B10 (RX1-), RN1.5 (R4.2)
unnamed: J1.A11 (RX2+), RN3.5 (R4.2)
unnamed: J1.A10 (RX2-), RN3.6 (R3.2)
unnamed: J1.A8 (SBU1), RN2.5 (R4.2)
unnamed: J1.B8 (SBU2), RN4.8 (R1.2)
unnamed: J1.A2 (TX1+), RN1.8 (R1.2)
unnamed: J1.A3 (TX1-), RN1.7 (R2.2)
unnamed: J1.B2 (TX2+), RN3.7 (R2.2)
unnamed: J1.B3 (TX2-), RN3.8 (R1.2)
unnamed: J1.A6 (D+), RN2.7 (R2.2)
unnamed: J1.A7 (D-), RN2.6 (R3.2)
unnamed: J1.B7 (D-), RN4.7 (R2.2)
unnamed: J1.B6 (D+), RN4.6 (R3.2)

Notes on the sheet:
sorry this is not as readable as you might want =D hopefully it conveys the idea though!

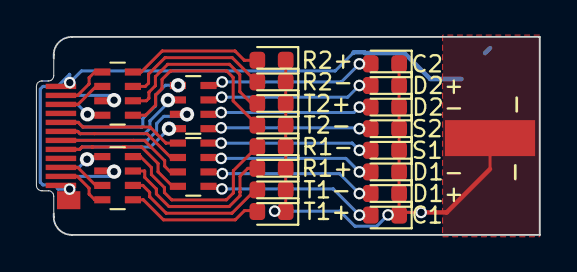
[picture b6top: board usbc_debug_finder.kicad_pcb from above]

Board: 2 copper layers, 28.0 x 11.0 mm, 22 parts (0 on the bottom side), 34 nets.

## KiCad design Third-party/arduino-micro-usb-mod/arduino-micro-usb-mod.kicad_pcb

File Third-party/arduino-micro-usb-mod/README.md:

# USB-B to MicroUSB adapter

[Original description from Scott Alfter](https://hackaday.io/project/161009-usb-micro-b-to-b-adapter-board):

> I had a clearance problem between the USB connector on an Arduino Mega and a
> RAMPS-FD 3D printer control shield, so I knocked together this adapter that
> lets you replace the full-size USB B connector on an Arduino (or pretty much
> any device that has such a connector) with a micro-B connector.
> 
> The design is intended to take a surface-mount right-angle connector, such
> as Molex part number 47346-0001.  Similar designs (such as Amphenol FCI part
> number 10118192-0001LF) may also work.  Designs that include through-hole
> mounting tabs won't work.
> 
> Put a jumper (either a small piece of wire or a zero-ohm 0805 "resistor") on
> JP1 if you want the host to be able to pass 5V through to the device.  For
> self-powered devices (as in the typical Arduino/RAMPS stack), you can leave
> JP1 unpopulated.

I made this board shorter for mechanical reasons, added a ground plane on the bottom layer and moved the VBUS jumper,
and a silkscreen description on the bottom.

This is a third-party board, the original source can be found here: https://gitlab.com/salfter/arduino-micro-usb-mod

- PCB size: 12.2*12.8
- Layer count: 2

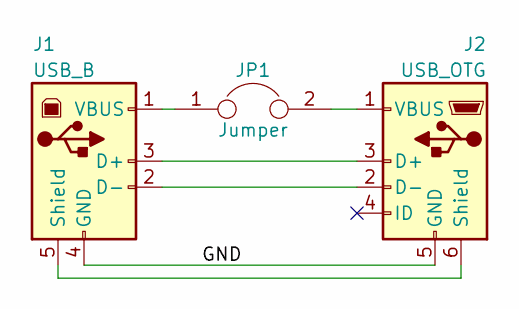
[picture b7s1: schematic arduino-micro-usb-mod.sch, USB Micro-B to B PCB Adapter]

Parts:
J1: USB_B
J2: USB_OTG; USB_Micro-B_Molex_47346-0001; Mfr PN 10118192-0001LF
JP1: Jumper; R_0805; Mfr PN RK73Z2ATTD

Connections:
/GND: J1.4 (GND), J2.5 (GND)
unnamed: J1.1 (VBUS), JP1.1
unnamed: J1.2 (D-), J2.2 (D-)
unnamed: J1.3 (D+), J2.3 (D+)
unnamed: J1.5 (Shield), J2.6 (Shield)
unnamed: J2.1 (VBUS), JP1.2

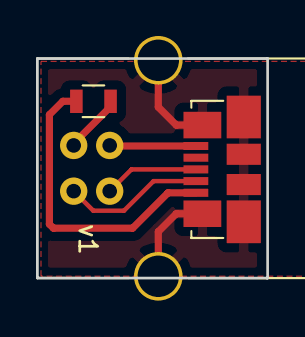
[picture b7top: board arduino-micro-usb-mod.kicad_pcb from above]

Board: 2 copper layers, 12.8 x 12.2 mm, 3 parts (0 on the bottom side), 6 nets.
